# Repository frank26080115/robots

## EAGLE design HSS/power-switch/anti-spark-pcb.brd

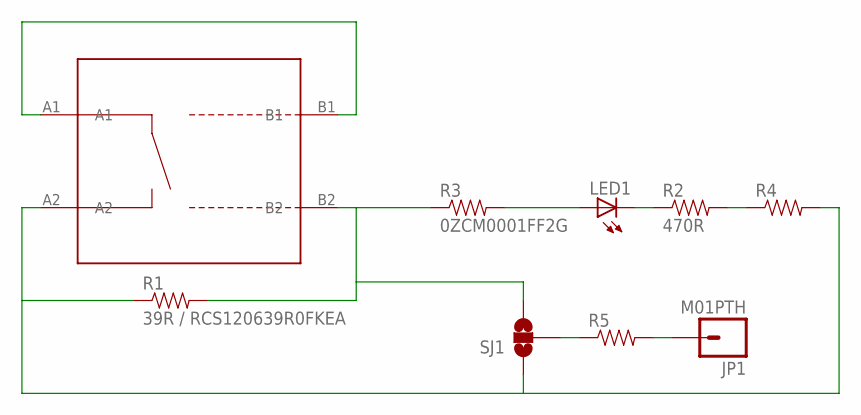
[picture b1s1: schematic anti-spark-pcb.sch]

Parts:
JP1: M01PTH; 1X01
LED1: LED1206; LED-1206
PCB1: KAKE-SWITCH-PCB
R1: 39R / RCS120639R0FKEA; 1206
R2: 470R; 0603-RES
R3: 0ZCM0001FF2G; 0603-RES
R4: RESISTOR0603-RES; 0603-RES
R5: RESISTOR1206; 1206
SJ1: SOLDERJUMPER_2WAYS; SJ_3

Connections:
unnamed: PCB1.B2, R1.2, R3.1, SJ1.3
unnamed: PCB1.A2, R1.1, R4.2, SJ1.1
unnamed: PCB1.A1, PCB1.B1
unnamed: LED1.A, R3.2
unnamed: R2.2, R4.1
unnamed: LED1.C, R2.1
unnamed: R5.1, SJ1.2
unnamed: JP1.1, R5.2

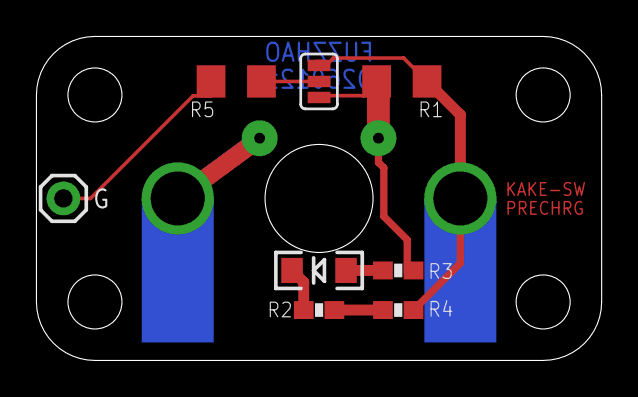
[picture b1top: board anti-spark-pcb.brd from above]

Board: 2 copper layers, 31.4 x 18.0 mm, 9 parts (0 on the bottom side), 8 nets.

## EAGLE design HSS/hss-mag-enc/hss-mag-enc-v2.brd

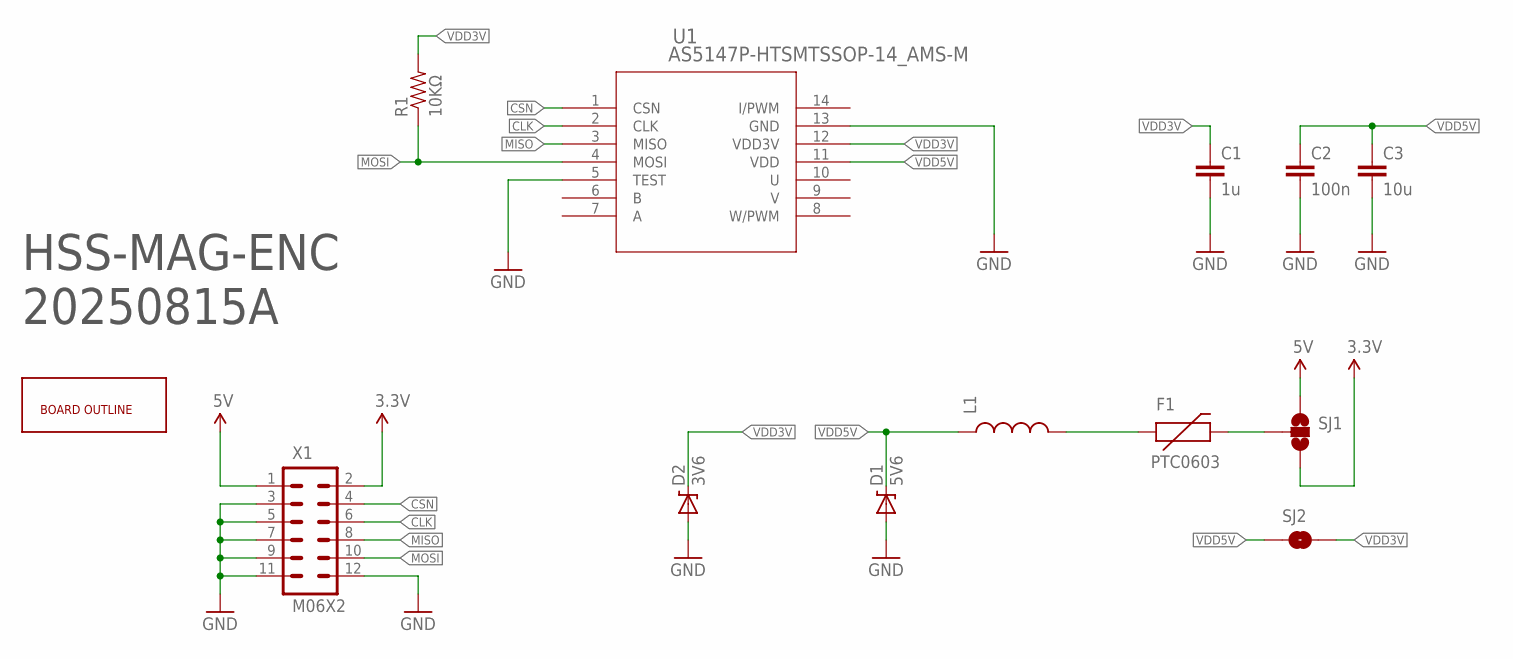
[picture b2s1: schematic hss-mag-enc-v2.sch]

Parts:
C1: 1u; 0805
C2: 100n; 0805
C3: 10u; 0805
D1: 5V6; SOD-323
D2: 3V6; SOD-323
F1: PTC0603; 0603
L1: INDUCTOR0805; 0805
R1: 10KΩ; 0603-RES
SJ1: SOLDERJUMPER_2WAYS; SJ_3
SJ2: SOLDERJUMPERNO; SJ_2S-NO
U1: AS5147P-HTSMTSSOP-14_AMS-M; TSSOP-14_AMS-M
U$1: BOARD-OUTLINE-V2; BOARD-OUTLINE-2
X1: M06X2; 2X6

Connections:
3.3V: SJ1.3, X1.2
5V: SJ1.1, X1.1
CLK: U1.2 (CLK), X1.6
CSN: U1.1 (CSN), X1.4
GND: C1.2, C2.2, C3.2, D1.2 (A), D2.2 (A), U1.5 (TEST), U1.13 (GND), X1.3, X1.5, X1.7, X1.9, X1.11, X1.12
MISO: U1.3 (MISO), X1.8
MOSI: R1.1, U1.4 (MOSI), X1.10
unnamed: F1.1, L1.2
unnamed: F1.2, SJ1.2
VDD3V: C1.1, D2.1 (C), R1.2, SJ2.2, U1.12 (VDD3V)
VDD5V: C2.1, C3.1, D1.1 (C), L1.1, SJ2.1, U1.11 (VDD)

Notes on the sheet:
HSS-MAG-ENC 20250815A

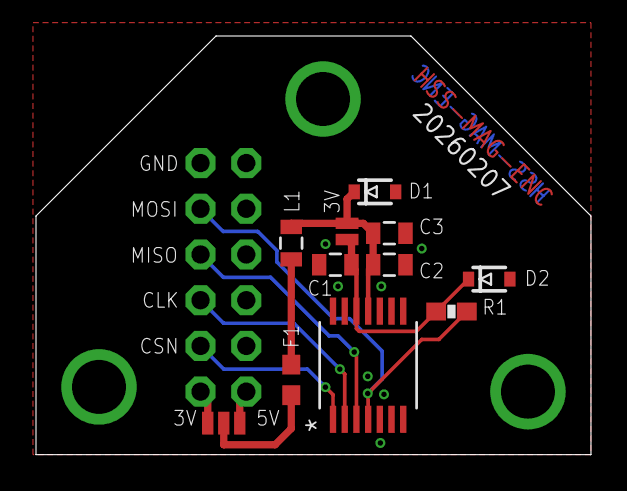
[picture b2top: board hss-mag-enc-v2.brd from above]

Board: 2 copper layers, 30.8 x 23.3 mm, 13 parts (1 on the bottom side), 11 nets.

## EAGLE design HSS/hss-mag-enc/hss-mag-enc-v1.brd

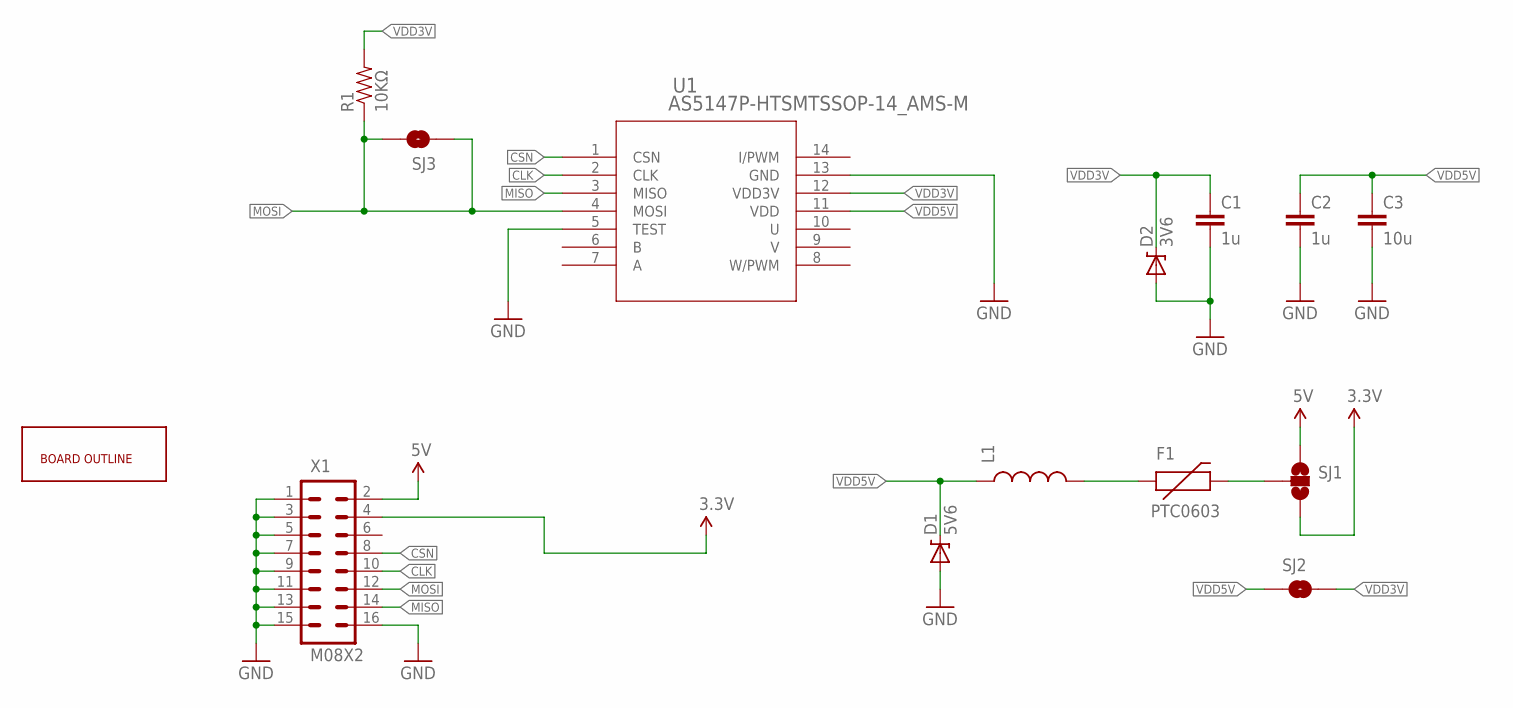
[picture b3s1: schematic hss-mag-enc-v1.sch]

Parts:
C1, C2: 1u; 0805
C3: 10u; 0805
D1: 5V6; SOD-323
D2: 3V6; SOD-323
F1: PTC0603; 0603
L1: INDUCTOR0805; 0805
R1: 10KΩ; 0603-RES
SJ1: SOLDERJUMPER_2WAYS; SJ_3
SJ2, SJ3: SOLDERJUMPERNO; SJ_2S-NO
U1: AS5147P-HTSMTSSOP-14_AMS-M; TSSOP-14_AMS-M
U$1: BOARD-OUTLINE-V1; BOARD-OUTLINE
X1: M08X2; 2X8

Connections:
3.3V: SJ1.3, X1.4
5V: SJ1.1, X1.2
CLK: U1.2 (CLK), X1.10
CSN: U1.1 (CSN), X1.8
GND: C1.2, C2.2, C3.2, D1.2 (A), D2.2 (A), U1.5 (TEST), U1.13 (GND), X1.1, X1.3, X1.5, X1.7, X1.9, X1.11, X1.13, X1.15, X1.16
MISO: U1.3 (MISO), X1.14
MOSI: R1.1, SJ3.1, SJ3.2, U1.4 (MOSI), X1.12
unnamed: F1.1, L1.2
unnamed: F1.2, SJ1.2
VDD3V: C1.1, D2.1 (C), R1.2, SJ2.2, U1.12 (VDD3V)
VDD5V: C2.1, C3.1, D1.1 (C), L1.1, SJ2.1, U1.11 (VDD)

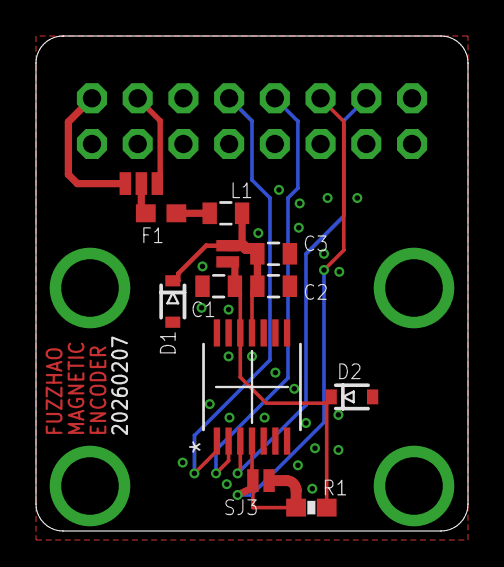
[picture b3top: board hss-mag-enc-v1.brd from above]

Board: 2 copper layers, 24.0 x 27.5 mm, 14 parts (0 on the bottom side), 11 nets.

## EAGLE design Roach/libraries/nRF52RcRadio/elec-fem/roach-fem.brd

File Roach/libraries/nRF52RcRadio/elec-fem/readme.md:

Roach FEM
=========

This is a front-end-module PCB that uses a Skyworks RFX2401C to amplify the signal from the nRF52840

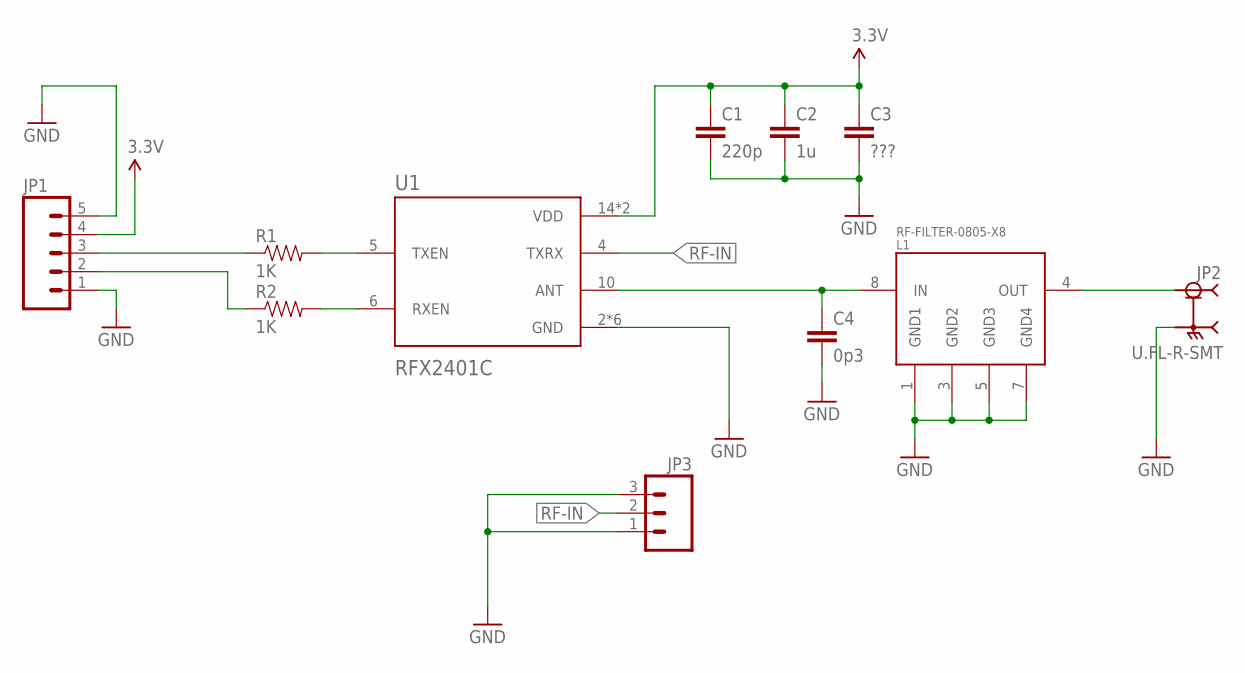
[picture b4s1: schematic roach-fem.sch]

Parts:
C1: 220p; 0603-CAP
C2: 1u; 0603-CAP
C3: ???; 0603-CAP
C4: 0p3; 0402-CAP
JP1: M05PTH; 1X05
JP2: U.FL-R-SMT; HRS_U.FL-R-SMT(10)
JP3: M03PTH; 1X03
L1: RF-FILTER-0805-X8; RF-FILTER-0805
R1, R2: 1K; 0603-RES
U1: RFX2401C; QFN50P300X300X60-17N

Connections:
3.3V: C1.1, C2.1, C3.1, JP1.4, U1.14 (VDD), U1.16 (VDD)
GND: C1.2, C2.2, C3.2, C4.2, JP1.1, JP1.5, JP2.2 (GND), JP2.3 (GND), JP3.1, JP3.3, L1.1 (GND1), L1.3 (GND2), L1.5 (GND3), L1.7 (GND4), U1.2 (GND), U1.3 (GND), U1.8 (GND), U1.9 (GND), U1.11 (GND), U1.17 (GND)
unnamed: JP1.3, R1.1
unnamed: JP1.2, R2.1
unnamed: R1.2, U1.5 (TXEN)
unnamed: R2.2, U1.6 (RXEN)
unnamed: C4.1, L1.8 (IN), U1.10 (ANT)
unnamed: JP2.1 (SIG), L1.4 (OUT)
RF-IN: JP3.2, U1.4 (TXRX)

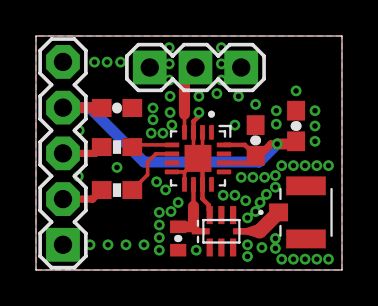
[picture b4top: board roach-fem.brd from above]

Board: 2 copper layers, 17.0 x 13.0 mm, 11 parts (0 on the bottom side), 9 nets.

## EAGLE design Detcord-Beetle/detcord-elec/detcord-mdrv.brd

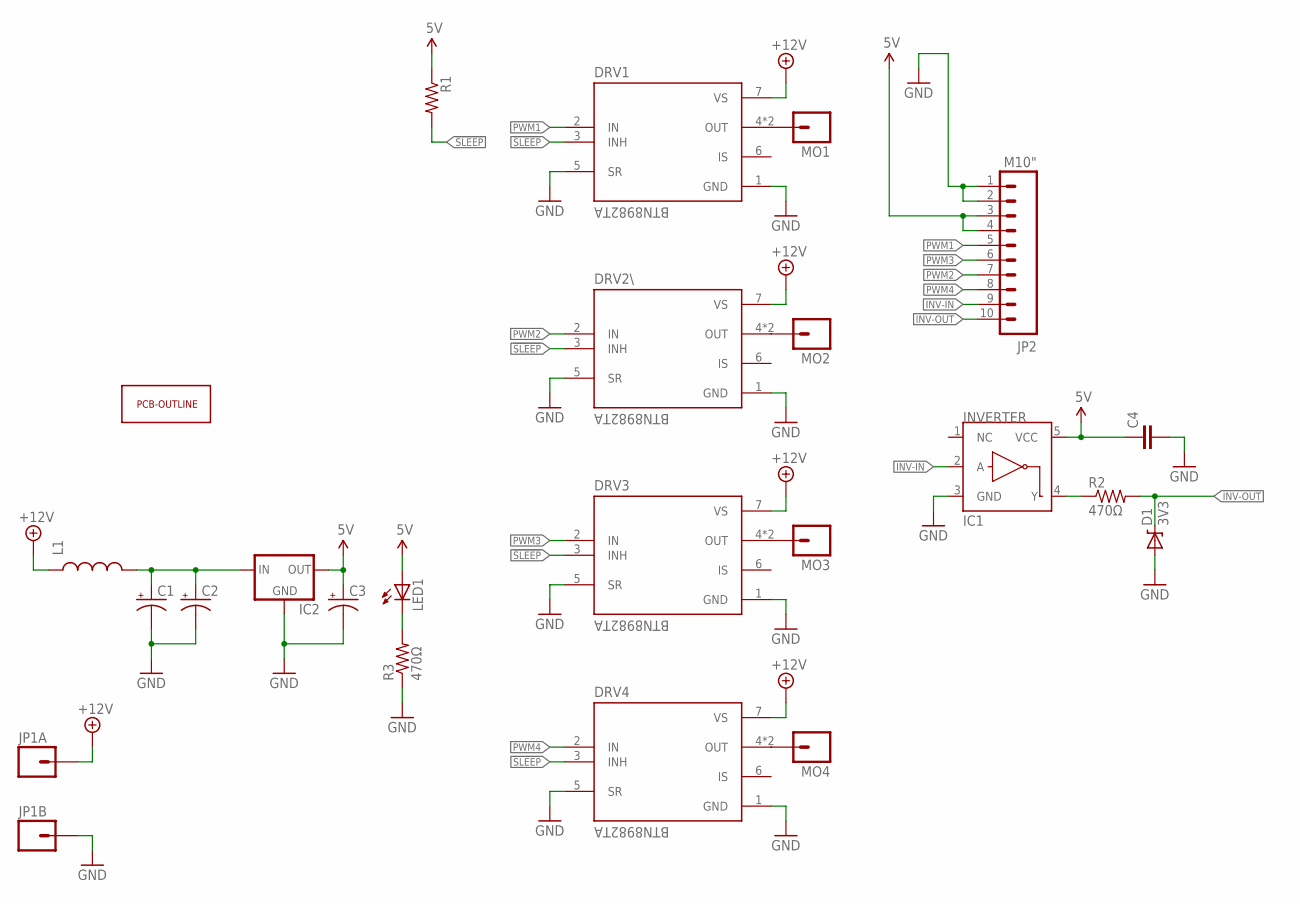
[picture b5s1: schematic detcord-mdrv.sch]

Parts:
C1, C2, C3: CAP_POLD; PANASONIC_D
C4: CAP0603-CAP; 0603-CAP
D1: 3V3; SOD-323
DRV1, DRV2\, DRV3, DRV4: BTN8982TA; DPAK127P1500X440-8N
IC1: INVERTER; SC70
IC2: V_REG_78XXSINK; TO220-IGO
JP1A, JP1B: M01PTH_2MM; 1X01_2MM
JP2: M10"; 1X10
L1: INDUCTORCR54; CR54
LED1: LED0603; LED-0603
MO1, MO2, MO3, MO4: M01PTH_2MM; 1X01_2MM
PCBOUTLINE1: PCB-OUTLINE-38X24MM
R1: RESISTOR0603-RES; 0603-RES
R2, R3: 470Ω; 0603-RES

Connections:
5V: C3.+, C4.1, IC1.5 (VCC), IC2.OUT, JP2.3, JP2.4, LED1.A, R1.1
!SLEEP: DRV1.3 (INH), DRV2\.3 (INH), DRV3.3 (INH), DRV4.3 (INH), R1.2
+12V: DRV1.7 (VS), DRV2\.7 (VS), DRV3.7 (VS), DRV4.7 (VS), JP1A.1, L1.P$1 (1)
GND: C1.-, C2.-, C3.-, C4.2, D1.2 (A), DRV1.1 (GND), DRV1.5 (SR), DRV2\.1 (GND), DRV2\.5 (SR), DRV3.1 (GND), DRV3.5 (SR), DRV4.1 (GND), DRV4.5 (SR), IC1.3 (GND), IC2.GND, JP1B.1, JP2.1, JP2.2, R3.1
INV-IN: IC1.2 (A), JP2.9
INV-OUT: D1.1 (C), JP2.10, R2.2
unnamed: C1.+, C2.+, IC2.IN, L1.P$2 (2)
unnamed: DRV1.4 (OUT), DRV1.8 (OUT), MO1.1
unnamed: DRV2\.4 (OUT), DRV2\.8 (OUT), MO2.1
unnamed: DRV3.4 (OUT), DRV3.8 (OUT), MO3.1
unnamed: DRV4.4 (OUT), DRV4.8 (OUT), MO4.1
unnamed: IC1.4 (Y), R2.1
unnamed: LED1.C, R3.2
PWM1: DRV1.2 (IN), JP2.5
PWM2: DRV2\.2 (IN), JP2.7
PWM3: DRV3.2 (IN), JP2.6
PWM4: DRV4.2 (IN), JP2.8

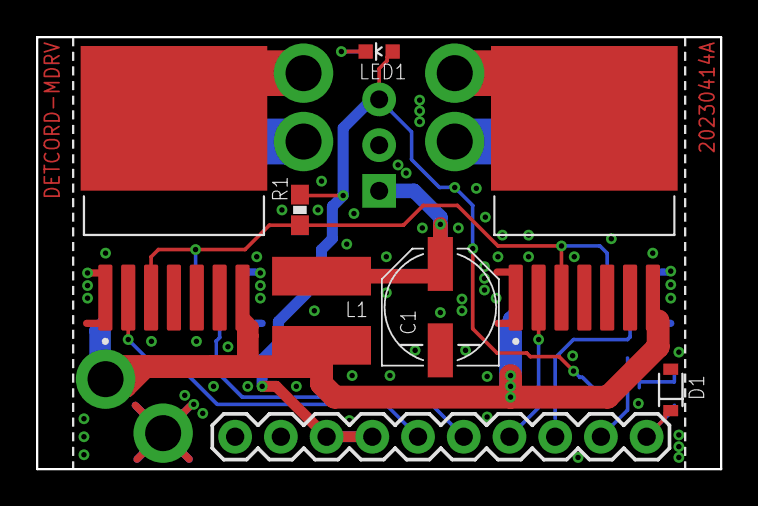
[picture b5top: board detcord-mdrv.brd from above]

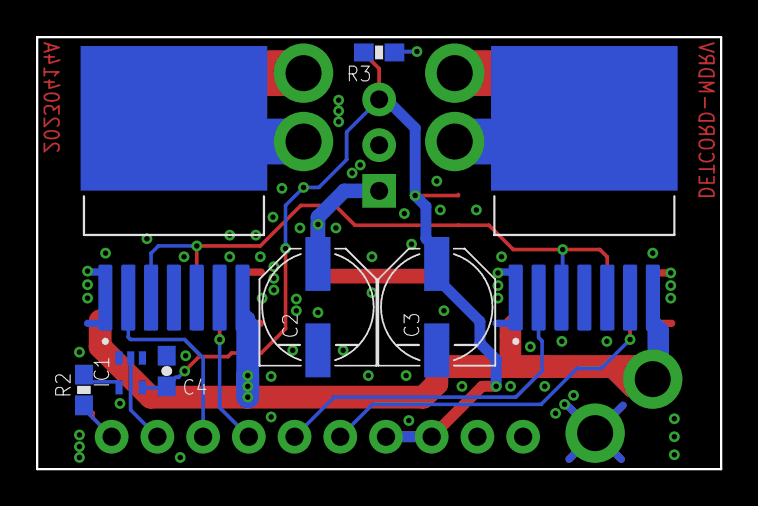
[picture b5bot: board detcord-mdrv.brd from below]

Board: 2 copper layers, 38.0 x 24.0 mm, 24 parts (8 on the bottom side), 17 nets.

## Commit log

2022-11-16 first edition
2023-03-19 taranis stuff
2023-03-30 q x7 config
2023-04-12 rx0 holder
2023-04-13 detcord beetle
2023-04-15 detcord elec
2023-04-15 detcord
2023-04-15 pathogen v1 archive
2023-04-15 detcord-mini archive
2023-04-16 esp32 rc radio
2023-04-16 esp32 rc radio smarter chan hop on rx side
2023-04-16 e32rcrad added bandwidth and tx pwr settings
2023-04-17 e32rcrad, more security, added bidir, added txtmsg
2023-04-17 e32rcrad attempt at improving performance
2023-04-18 e32rcrad more attempts at improving reliability
2023-04-27 roach wip
2023-04-27 nrf52 raw radio for roach
2023-04-27 roach code move preparation
2023-04-27 Roach code move
2023-04-27 roach pid
2023-04-28 esp32 rc radio tweaked tx timings
2023-04-28 esp32 rc radio added single chan rx mode
2023-04-29 e32rcrad debug pin assignment
2023-05-01 nRF5Rand
2023-05-01 nrf52rcradio wip
2023-05-01 RoachIMU builds
2023-05-01 added flush to rand generator
2023-05-02 roachusbmsd
2023-05-03 roach fem
2023-05-03 roach handheld tx
2023-05-03 roachusbmsd added way to detect vbus
2023-05-03 roachrotaryencoder added qdec for nrf52
2023-05-03 roachrotaryencoder builds
2023-05-03 Created RoachButton
2023-05-04 roach nonblockingtwi
2023-05-04 roachimu fixed pin mapping lookup
2023-05-04 nonblocking adafruit oled
2023-05-04 roach started working on menu
2023-05-05 nrf52rcradio tested
2023-05-05 AsyncAdc added nRF52 support
2023-05-05 nrf52 fixed asyncadc ending and added asyncadc example
2023-05-05 RoachCmdLine
2023-05-06 roach transmitter progress
2023-05-07 roach tx wip
2023-05-08 roach code compiles without error, not tested
2023-05-09 roach tx got the OLED working, menu seems to work
2023-05-10 roach tx wip, fem pins, usb msd choice
2023-05-10 roachtx wip
2023-05-10 roachrobot start
2023-05-11 detcord tweaks, new weap, imu mount
2023-05-11 roachusbmsd added way to check last access time
2023-05-11 roach robot lib wip
2023-05-12 detcord beetle wip
2023-05-13 roach radio added connection state for rx
2023-05-13 detcord use a bigger 2826 motor
2023-05-14 detcord deadshaft
2023-05-14 detcord tweaks
2023-05-15 detcord wheel mold
2023-05-18 roach imu use nbtwi
2023-05-20 roach RNG code updated to be cleaner
2023-05-21 nrf52 radio fixed bugs caused by softdevice
2023-05-21 nRF52RcRadio, anti replay attack, pairing
2023-05-22 roach doc
2023-05-22 roach tx mech thicker cover plate, fixed enc hole spacing
2023-05-23 roach doc and hop schedule change
2023-05-25 roach support platformio
2023-05-25 nRF52RcRadio cleaned up code a bit
2023-05-25 roach a few compiler warnings
2023-05-28 roach pot added way to set adc ref
2023-05-28 roach radio wip
2023-06-06 detcord beetle mfg files update
2023-06-06 roach handheld tx mech mfg
2023-06-07 work towards roach robot side library code
2023-06-09 roach robot wip
2023-06-14 roach mech changes
2023-06-15 adafruit oled drawasneeded untested
2023-06-15 roach hw bringup started
2023-06-17 detcord new bearings
2023-06-17 charger box mount for ammo box
2023-06-17 4x battery protector
2023-06-17 handheld tx added a friction pad for heading wheel
2023-06-17 roach more hw bringup fixes
2023-06-18 added RoachServo
2023-06-18 minor 3d print changes
2023-06-23 roach oled bringup
2023-06-23 roach button now uses polling
2023-06-23 roach + detcord mech changes
2023-06-23 started detcord fw
2023-06-24 roachimu actually bench tested
2023-06-25 roachbutton fixed interrupt
2023-06-25 roachservo tested
2023-06-25 roachimu orientation and failure improvements
2023-06-25 roachimu state machine setup added delays
2023-06-26 roachimu filtering + logger
2023-06-26 nrf52rcradio more useful session ID management
2023-06-26 roach heading manager
2023-06-27 roachimu can log extra data
2023-06-27 roach heading manager wip
2023-06-29 mrf52onewireserial
2023-06-29 nrf52onewireserial
2023-06-29 blhelipassthru untested
2023-06-29 roachpid syntax error
2023-07-01 nrfows added hw mode
2023-07-01 detcord fw wip
2023-07-01 roachheartbeat wip, wdt tested
2023-07-02 roachheartbeat tested
2023-07-02 roachheartbeat added DMA PWM mode for neopix
2023-07-03 RoachServo added way to slowing ramp up speed
2023-07-03 RoachHeartbeat added HardwarePWM->takeOwnership
2023-07-03 roach detcord code wip
2023-07-03 roachservo prevent invalid ramp step
2023-07-03 roachheartbeat added hue, untested
2023-07-06 nRF52OneWireSerial added echo and end
2023-07-07 esclink testing
2023-07-07 am32 assistance tools
2023-07-08 am32 hw analyzer working, voltage and current not working
2023-07-09 am32-hw-analyzer finishing up
2023-07-09 nrf52dshot wip
2023-07-09 roachheartbeat hue improvements
2023-07-09 nrf52dshot tested
2023-07-09 roachheartbeat added example
2023-07-09 roach math fixed map bug
2023-07-09 detcord pulleys STL record set
2023-07-11 more work on am32 tools
2023-07-11 nrf52dshot api similar to servo
2023-07-11 am32 web tool, need to go home and test
2023-07-12 am32 web tool fully working
2023-07-15 detcord mech
2023-07-15 moved am32 helpers
2023-07-15 nrfows added debug pin
2023-07-16 detcord ESC FW image
2023-07-16 detcord esc fw eeprom current limit 65A
2023-07-22 detcord mech changes, extra screws in front
2023-07-22 detcord wheels radius bigger by 1.5mm
2023-07-22 detcord weap esc better bootloader
2023-07-22 nrf52onewireserial reliability testing
2023-07-22 nrf52onewireserial reliability useless code removed
2023-07-23 roach, esc link app, inversion detection, wip
2023-07-29 servo tester for roach wip
2023-08-02 roach servo tester working
2023-08-02 update am32 image for aria esc
2023-08-03 am32 firmware change default eeprom layout version
2023-08-03 am32 fw eep enabled brake on stop
2023-08-04 detcord mech sendcutsend order 3
2023-08-04 cell equalizer box
2023-08-04 detcord 3d print record
2023-08-05 nrf52 uicr writer
2023-08-07 roachfailsafe draft
2023-08-08 detcord wip
2023-08-08 roach robot task manager wip
2023-08-08 roach rgb led for xiao ble
2023-08-08 renamed roach imu file to indicate which chip
2023-08-08 roachimu lsm6ds3 started work
2023-08-09 roachimu work on LSM6DS3 code
2023-08-09 detcord heartbeat added CB mode for XIAO
2023-08-09 nonblockingtwi added option for slow mode
2023-08-09 added a list of Roach related libraries
2023-08-10 roach detcord fw wip, documented a ton of math stuff
2023-08-10 roachimu use constants, added reversed angle orientation
2023-08-10 roach detcord fw wip, sync, angle units, MSD
2023-08-11 roach detcord fw wip
2023-08-14 roach ctrl fw wip
2023-08-14 roach tx fw wip
2023-08-15 roach tx fw wip fixed menu list scroll
2023-08-15 roach tx fw wip trying to fix encoder and nvm val change
2023-08-16 fixed roach button not being immediately responsive
2023-08-16 detcord xiao platformio
2023-08-16 roach tx fw wip, fix fs iteration
2023-08-16 detcord fw adding xiao pins
2023-08-16 roach tx fw, disabled repeat mode on toggle switches
2023-08-16 roach detcord fw added debug msg for rosync
2023-08-16 roachbutton added statistics for isr
2023-08-16 detcord fw added debug messages for nvm
2023-08-16 detcord fw trying to setup debug logging
2023-08-17 roach detcord fw, XIAO flash IC support
2023-08-17 detcord XIAO IMU I2C
2023-08-17 detcord xiao flash ic compile error fix
2023-08-17 detcord imu calibration
2023-08-18 detcord imu not working but I need to go home
2023-08-18 detcord xiao gyro calib works
2023-08-18 roachimu lsm added angle calib
2023-08-18 roachimu motionless auto calibration
2023-08-18 roachimu_lsm seemed to fix the timeout issue
2023-08-18 detcord fixing imu reliability again
2023-08-19 roachrctx fw fixed file write bug
2023-08-20 roachrctx fw wip, fixed file load, more calib changes
2023-08-20 added watchdog feed to flash mem functions
2023-08-21 roachrctx fw fixed file not loading, calib menu changes
2023-08-21 detcord mech some oddball 3d printed armor parts
2023-08-21 detcord roach code in bad state
2023-08-23 servotester added pwm for weap
2023-08-27 detcord last two variations of weap hub pulley
2023-08-27 detcord last mech changes before total rework
2023-08-27 started new detcord design
2023-08-28 detcord new mech
2023-08-29 detcord mech wip
2023-08-30 detcord mech wip, added aux holes to plates
2023-08-30 detcord mech widened battery compartment
2023-08-30 old-detcord stuff
2023-08-31 detcord mech changes
2023-08-31 detcord mech minor changes
2023-09-03 Bleed
2023-09-03 detcord printing test chassis
2023-09-04 Bleed mech wip
2023-09-06 detcord v3 test design sent to laser
2023-09-09 detcord wheel balance
2023-09-14 EdgeTX graphics
2023-09-14 detcord minor wheel spacing changes in chassis
2023-09-14 detcord-mini wip
2023-09-14 Bleed wip
2023-09-17 detcord minor changes, better for mfg
2023-09-18 detcord wheel mold printed
2023-09-18 detcord-jr mass and size validated
2023-09-19 detcord wheel wip
2023-10-23 laceration wip
2023-10-23 detcord wheel hub made with tube
2023-10-28 Laceration changed to M4 standoffs on side armour
2023-10-28 Laceration deleted suppressed screws from prev update
2023-10-29 Laceration, weap bearing retainer changed to washer
2023-11-01 Laceration repositioned butt screws
2023-11-01 Laceration blade hugs bearing
2023-11-02 Laceration slightly lighter materials
2023-12-07 some ELRS firmware builds
2023-12-07 elrs firmware, differentiated wifi vs uart for RX
2023-12-07 elrs rx firmware version name change
2026-01-03 hss anti spark pcb for kake switch
2026-02-08 uncommitted PCBs
2026-02-09 laceration v3 some files
2026-02-11 update laceration v3 dxfs
2026-02-11 laceration-v3 stacked weapon pulley 20mm
2026-02-11 update laceration v3 files
2026-02-11 more laceration v3 files
2026-02-12 laceration v3 changed motor mount geo
2026-02-12 laceration v3 changes, chassis, ar500 armour
2026-02-13 fork lengths, slotted holes in pulley disk
2026-02-13 rename
2026-03-17 laceration v3 mfg files update

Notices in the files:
parts and their libraries:
COPYRIGHT: Copyright (C) 2025 Ultra Librarian. All rights reserved.
